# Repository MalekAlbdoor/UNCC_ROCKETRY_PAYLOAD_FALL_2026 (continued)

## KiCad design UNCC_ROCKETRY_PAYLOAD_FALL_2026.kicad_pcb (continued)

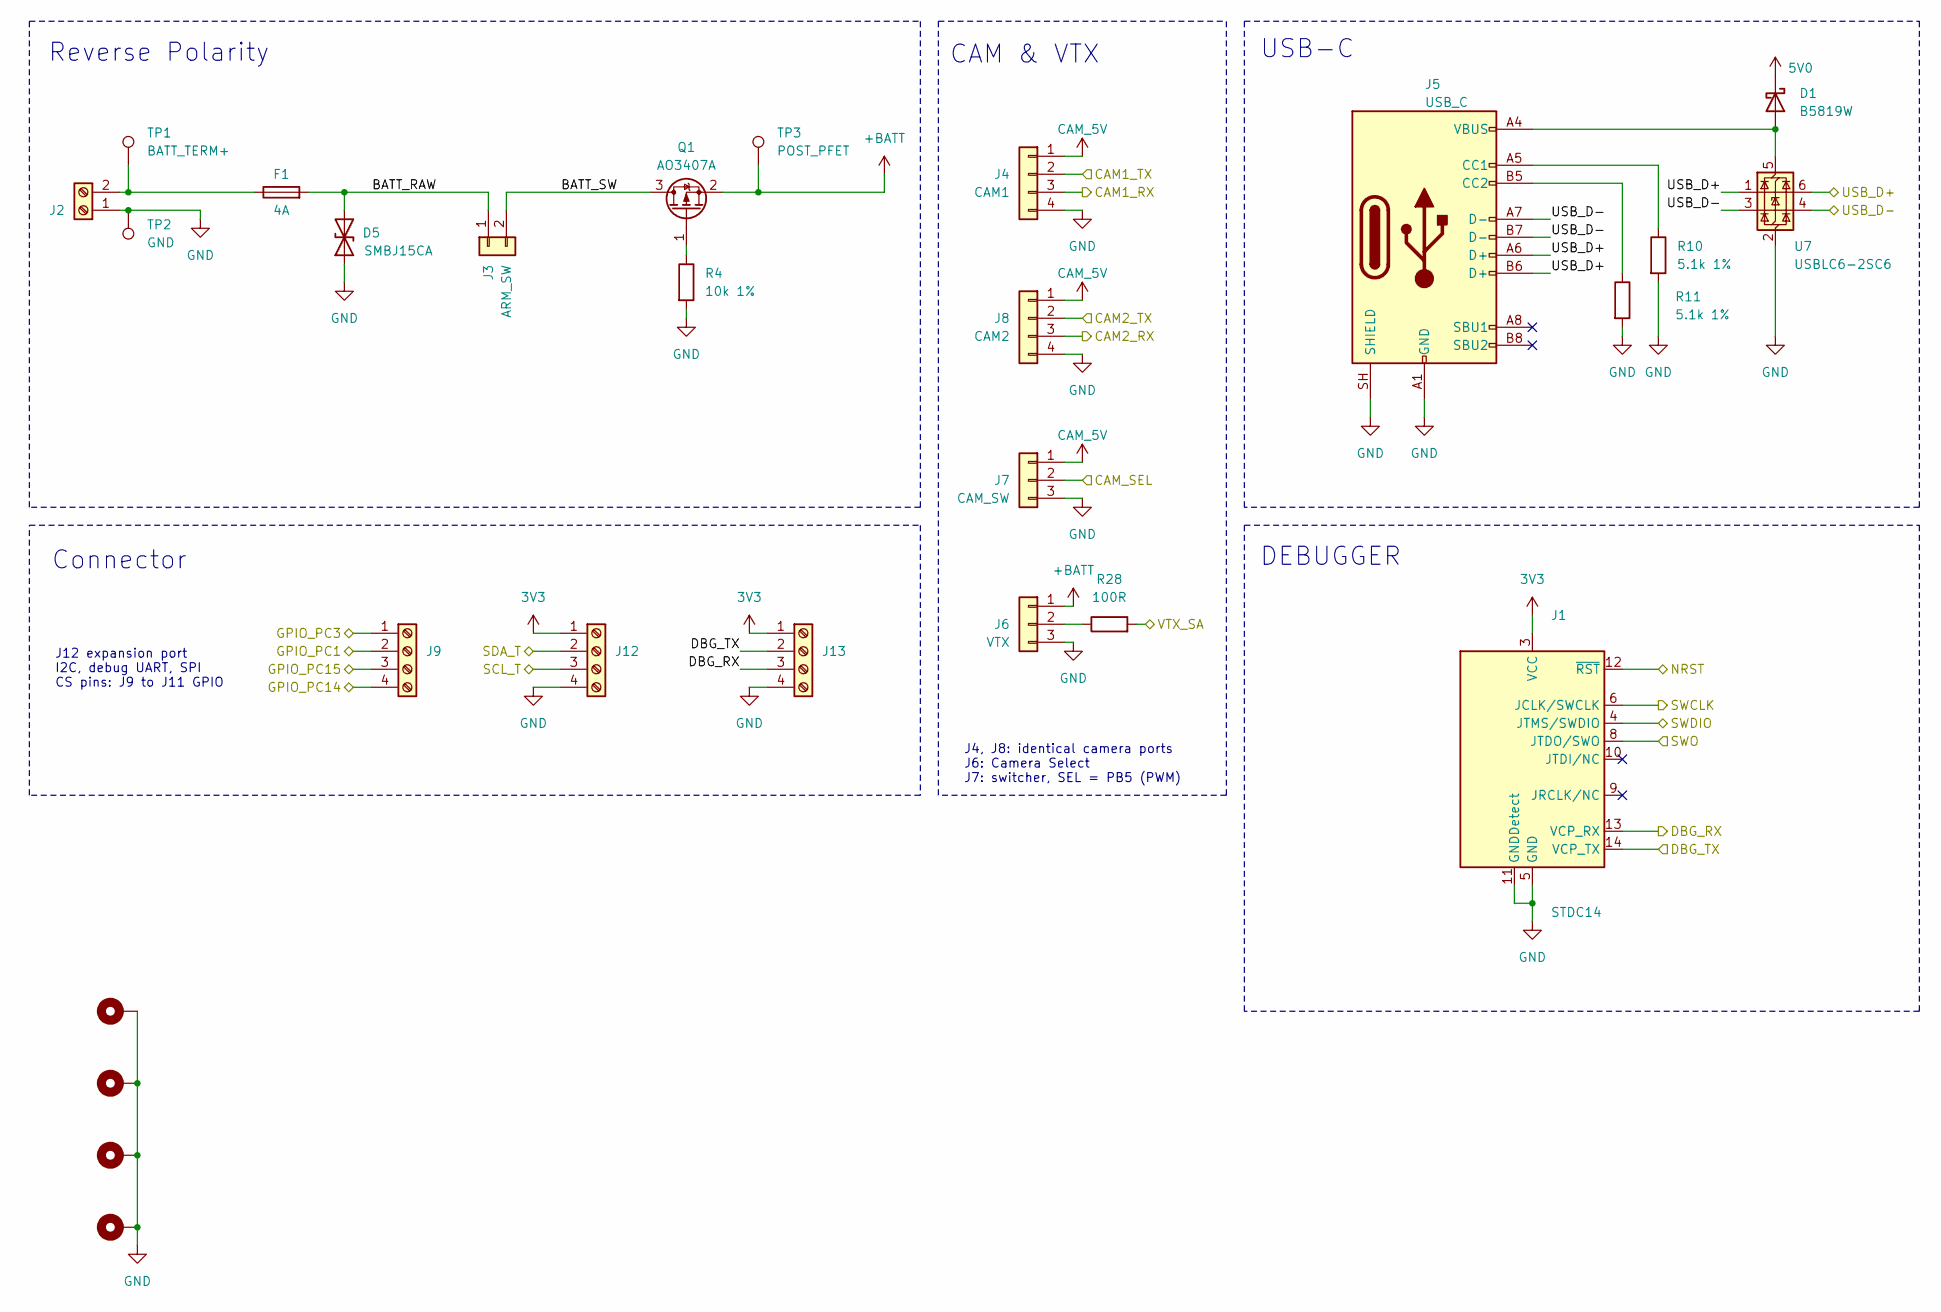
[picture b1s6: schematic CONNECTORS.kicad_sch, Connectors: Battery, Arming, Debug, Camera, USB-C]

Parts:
D1: B5819W; D_SOD-123; MPN B5819W; LCSC C7420330
D5: SMBJ15CA; D_SMB; MPN SMBJ15CA; LCSC C2760879
F1: 4A; Fuse_Littelfuse-NANO2-451_453; MPN 0451004.MRL; LCSC C27515
H2, H3, H4, H5: MountingHole_Pad; MountingHole_3.2mm_M3_Pad
J1: STDC14; PinHeader_2x07_P1.27mm_Vertical_SMD
J2: BATT; JST_XH_B2B-XH-A_1x02_P2.50mm_Vertical; MPN B2B-XH-A
J3: ARM_SW; JST_XH_B2B-XH-A_1x02_P2.50mm_Vertical; MPN B2B-XH-A
J4: CAM1; JST_PH_B4B-PH-K_1x04_P2.00mm_Vertical; MPN B4B-PH-K
J5: USB_C; USB_C_Receptacle_HRO_TYPE-C-31-M-12; MPN TYPE-C-31-M-12
J6: VTX; JST_XH_B3B-XH-A_1x03_P2.50mm_Vertical; MPN B3B-XH-A
J7: CAM_SW; JST_PH_B3B-PH-K_1x03_P2.00mm_Vertical; MPN B3B-PH-K
J8: CAM2; JST_PH_B4B-PH-K_1x04_P2.00mm_Vertical; MPN B4B-PH-K
J9, J12, J13: Screw_Terminal_01x04; TerminalBlock_Phoenix_PT-1,5-4-3.5-H_1x04_P3.50mm_Horizontal; MPN PT 1,5/4-3.5-H
Q1: AO3407A; SOT-23; MPN AO3407A; LCSC C347478
R4: 10k 1%; R_0603_1608Metric_Pad0.98x0.95mm_HandSolder; MPN 0603WAF1002T5E; LCSC C25804
R10, R11: 5.1k 1%; R_0603_1608Metric_Pad0.98x0.95mm_HandSolder; MPN 0603WAF5101T5E; LCSC C23186
R28: 100R; R_0603_1608Metric_Pad0.98x0.95mm_HandSolder; MPN 0603WAF1000T5E; LCSC C22775
TP1: BATT_TERM+; TestPoint_Pad_D1.5mm
TP2: GND; TestPoint_Pad_D1.5mm
TP3: POST_PFET; TestPoint_Pad_D1.5mm
U7: USBLC6-2SC6; SOT-23-6; MPN USBLC6-2SC6; LCSC C2827654

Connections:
3V3: J1.3 (VCC), J12.1, J13.1; also elsewhere on the board
5V0: D1.1 (K); also elsewhere on the board
+BATT: J6.1, Q1.2 (S), TP3.1 (1_1); also elsewhere on the board
/CONNECTORS/BATT_RAW: D5.2 (A2), F1.2, J3.1
/CONNECTORS/BATT_SW: J3.2, Q1.3 (D)
/CONNECTORS/CAM1_RX: J4.3; also elsewhere on the board
/CONNECTORS/CAM1_TX: J4.2; also elsewhere on the board
/CONNECTORS/CAM2_RX: J8.3; also elsewhere on the board
/CONNECTORS/CAM2_TX: J8.2; also elsewhere on the board
/CONNECTORS/CAM_SEL: J7.2; also elsewhere on the board
/CONNECTORS/DBG_RX: J1.13 (VCP_RX), J13.3; also elsewhere on the board
/CONNECTORS/DBG_TX: J1.14 (VCP_TX), J13.2; also elsewhere on the board
/CONNECTORS/GPIO_PC1: J9.2; also elsewhere on the board
/CONNECTORS/GPIO_PC3: J9.1; also elsewhere on the board
/CONNECTORS/GPIO_PC14: J9.4; also elsewhere on the board
/CONNECTORS/GPIO_PC15: J9.3; also elsewhere on the board
/CONNECTORS/NRST: J1.12 (~RST); also elsewhere on the board
/CONNECTORS/SWCLK: J1.6 (JCLK/SWCLK); also elsewhere on the board
/CONNECTORS/SWDIO: J1.4 (JTMS/SWDIO); also elsewhere on the board
/CONNECTORS/SWO: J1.8 (JTDO/SWO); also elsewhere on the board
/CONNECTORS/USB_D+: J5.A6 (D+), J5.B6 (D+), U7.1 (I/O1), U7.6 (I/O1); also elsewhere on the board
/CONNECTORS/USB_D-: J5.A7 (D-), J5.B7 (D-), U7.3 (I/O2), U7.4 (I/O2); also elsewhere on the board
/CONNECTORS/VTX_SA: R28.2; also elsewhere on the board
/SCL_T: J12.3; also elsewhere on the board
/SDA_T: J12.2; also elsewhere on the board
CAM_5V: J4.1, J7.1, J8.1; also elsewhere on the board
GND: D5.1 (A1), H2.1 (1_1), H3.1 (1_1), H4.1 (1_1), H5.1 (1_1), J1.5 (GND), J1.7 (GND), J1.11 (GNDDetect), J2.1, J4.4, J5.A1 (GND), J5.A12 (GND), J5.B1 (GND), J5.B12 (GND), J5.SH (SHIELD), J6.3, J7.3, J8.4, J12.4, J13.4, R4.2, R10.2, R11.2, TP2.1 (1_1), U7.2 (GND); also elsewhere on the board
unnamed: D1.2 (A), J5.A4 (VBUS), J5.A9 (VBUS), J5.B4 (VBUS), J5.B9 (VBUS), U7.5 (VBUS)
unnamed: F1.1, J2.2, TP1.1 (1_1)
unnamed: J5.A5 (CC1), R10.1
unnamed: J5.B5 (CC2), R11.1
unnamed: J6.2, R28.1
unnamed: Q1.1 (G), R4.1

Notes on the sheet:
USB-C
Reverse Polarity
CAM & VTX
DEBUGGER
Connector
J12 expansion port I2C, debug UART, SPI CS pins: J9 to J11 GPIO
J4, J8: identical camera ports J6: Camera Select J7: switcher, SEL = PB5 (PWM)

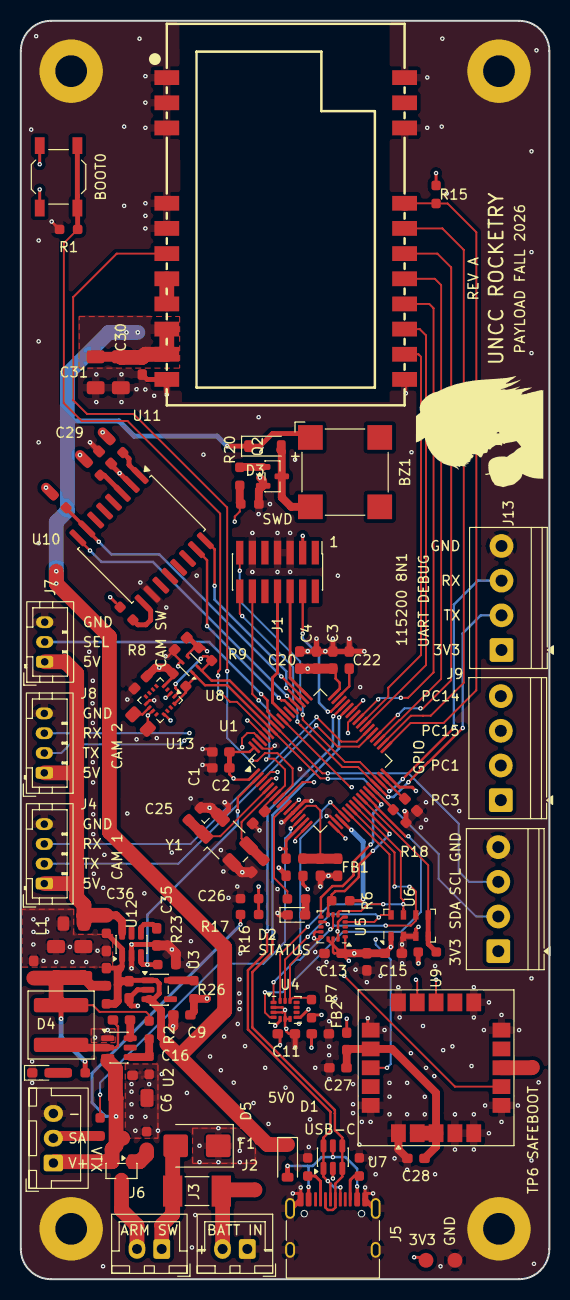
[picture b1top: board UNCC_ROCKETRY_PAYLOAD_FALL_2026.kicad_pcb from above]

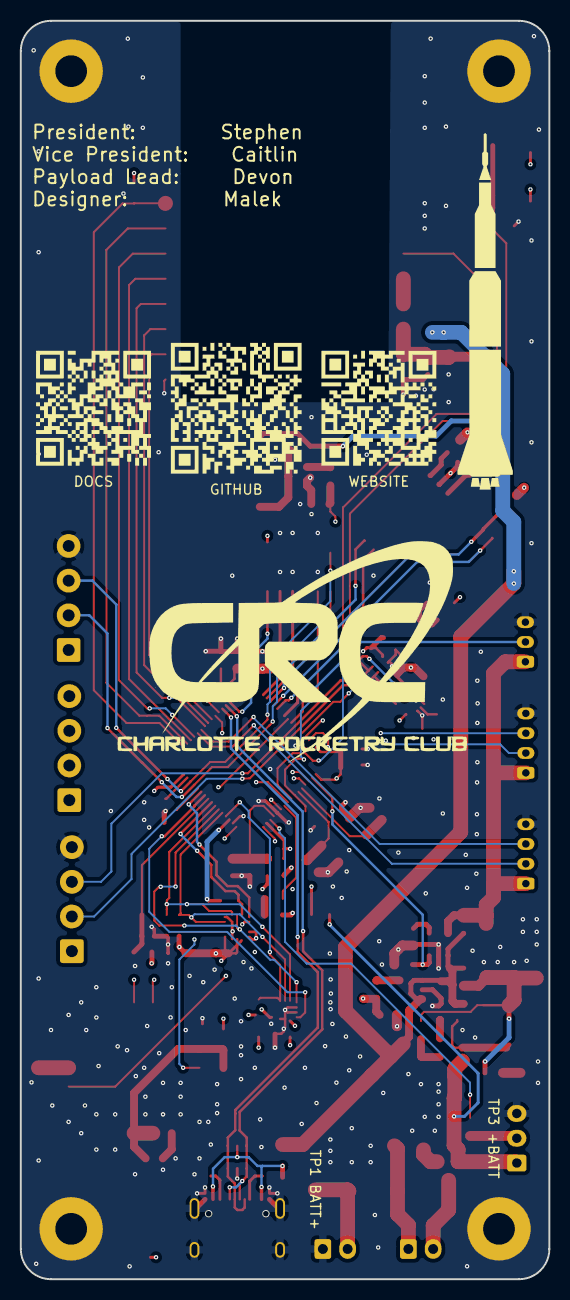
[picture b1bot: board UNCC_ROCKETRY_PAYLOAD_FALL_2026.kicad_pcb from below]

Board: 4 copper layers, 53.3 x 127.0 mm, 120 parts (5 on the bottom side), 85 nets.

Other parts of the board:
LOGO1: CRC_Logo
LOGO2: Silhouette_Logo
LOGO3: Saturn_V
LOGO4: QR_Website
LOGO5: QR_Repo
LOGO6: QR_Docs

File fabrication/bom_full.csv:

Qty,Designators,Value,Footprint,Manufacturer,MPN,LCSC,Assembly,Link
1,BZ1,CMT-8504-100-SMT,MagneticBuzzer_CUI_CMT-8504-100-SMT,CUI Devices,CMT-8504-100-SMT-TR,C22359707,JLC places,https://www.lcsc.com/search?q=C22359707
18,"C1,C2,C3,C4,C5,C7,C10,C11,C12,C13,C14,C15,C16,C24,C27,C29,C32,C33",100nF,C_0603_1608Metric_Pad1.08x0.95mm_HandSolder,YAGEO,CC0603KRX7R9BB104,C14663,JLC places,https://www.lcsc.com/search?q=C14663
1,C6,10uF 25V,C_1206_3216Metric_Pad1.33x1.80mm_HandSolder,Samsung,CL31A106KBHNNNE,C13585,JLC places,https://www.lcsc.com/search?q=C13585
5,"C8,C9,C23,C34,C38",1uF,C_0603_1608Metric_Pad1.08x0.95mm_HandSolder,Samsung,CL10A105KB8NNNC,C15849,JLC places,https://www.lcsc.com/search?q=C15849
1,C17,75pF,C_0603_1608Metric_Pad1.08x0.95mm_HandSolder,YAGEO,CC0603JRNPO9BN750,C282074,JLC places,https://www.lcsc.com/search?q=C282074
4,"C18,C19,C30,C31",22uF,C_1206_3216Metric_Pad1.33x1.80mm_HandSolder,Samsung,CL31A226KAHNNNE,C12891,JLC places,https://www.lcsc.com/search?q=C12891
2,"C20,C28",4.7uF 10V,C_0603_1608Metric_Pad1.08x0.95mm_HandSolder,Samsung,CL10A475KO8NNNC,C19666,JLC places,https://www.lcsc.com/search?q=C19666
2,"C21,C22",2.2uF 10V,C_0603_1608Metric_Pad1.08x0.95mm_HandSolder,Samsung,CL10A225KO8NNNC,C23630,JLC places,https://www.lcsc.com/search?q=C23630
2,"C25,C26",12pF C0G,C_0603_1608Metric_Pad1.08x0.95mm_HandSolder,Samsung,CL10C120JB8NNNC,C38523,JLC places,https://www.lcsc.com/search?q=C38523
1,C35,1nF,C_0603_1608Metric_Pad1.08x0.95mm_HandSolder,Samsung,CL10B102KB8NNNC,C1588,JLC places,https://www.lcsc.com/search?q=C1588
2,"C36,C37",10uF,C_0805_2012Metric_Pad1.18x1.45mm_HandSolder,Samsung,CL21A106KAYNNNE,C15850,JLC places,https://www.lcsc.com/search?q=C15850
2,"D1,D3",B5819W,D_SOD-123,,B5819W,C7420330,JLC places,https://www.lcsc.com/search?q=C7420330
1,D2,Green,LED_0603_1608Metric_Pad1.05x0.95mm_HandSolder,Everlight,19-217/G7C-AN1P2/6T,C2986030,JLC places,https://www.lcsc.com/search?q=C2986030
1,D4,Red,LED_0603_1608Metric_Pad1.05x0.95mm_HandSolder,Hubei KENTO,KT-0603R,C2286,JLC places,https://www.lcsc.com/search?q=C2286
1,D5,SMBJ15CA,D_SMB,,SMBJ15CA,C2760879,JLC places,https://www.lcsc.com/search?q=C2760879
1,F1,4A,Fuse_Littelfuse-NANO2-451_453,Littelfuse,0451004.MRL,C27515,JLC places,https://www.lcsc.com/search?q=C27515
2,"FB1,FB2",600R@100MHz,L_0603_1608Metric_Pad1.05x0.95mm_HandSolder,Sunlord,GZ1608D601TF,C1002,JLC places,https://www.lcsc.com/search?q=C1002
1,J1,STDC14,PinHeader_2x07_P1.27mm_Vertical_SMD,,,,hand solder,
1,J2,BATT,JST_XH_B2B-XH-A_1x02_P2.50mm_Vertical,JST,B2B-XH-A,,hand solder,
1,J3,ARM_SW,JST_XH_B2B-XH-A_1x02_P2.50mm_Vertical,JST,B2B-XH-A,,hand solder,
1,J4,CAM1,JST_PH_B4B-PH-K_1x04_P2.00mm_Vertical,JST,B4B-PH-K,,hand solder,
1,J5,USB_C,USB_C_Receptacle_HRO_TYPE-C-31-M-12,HRO,TYPE-C-31-M-12,,hand solder,
1,J6,VTX,JST_XH_B3B-XH-A_1x03_P2.50mm_Vertical,JST,B3B-XH-A,,hand solder,
1,J7,CAM_SW,JST_PH_B3B-PH-K_1x03_P2.00mm_Vertical,JST,B3B-PH-K,,hand solder,
1,J8,CAM2,JST_PH_B4B-PH-K_1x04_P2.00mm_Vertical,JST,B4B-PH-K,,hand solder,
3,"J9,J12,J13",Screw_Terminal_01x04,"TerminalBlock_Phoenix_PT-1,5-4-3.5-H_1x04_P3.50mm_Horizontal",Phoenix Contact,"PT 1,5/4-3.5-H",,hand solder,
1,L1,10uH,L_Wuerth_XHMI-6060,Wurth Elektronik,74439346100,C2651185,JLC places,https://www.lcsc.com/search?q=C2651185
1,Q1,AO3407A,SOT-23,Alpha & Omega,AO3407A,C347478,JLC places,https://www.lcsc.com/search?q=C347478
1,Q2,AO3400A,SOT-23,Alpha & Omega,AO3400A,C20917,JLC places,https://www.lcsc.com/search?q=C20917
11,"R1,R4,R5,R6,R7,R12,R13,R14,R15,R18,R27",10k 1%,R_0603_1608Metric_Pad0.98x0.95mm_HandSolder,UniOhm,0603WAF1002T5E,C25804,JLC places,https://www.lcsc.com/search?q=C25804
4,"R2,R16,R21,R23",100k 1%,R_0603_1608Metric_Pad0.98x0.95mm_HandSolder,UniOhm,0603WAF1003T5E,C25803,JLC places,https://www.lcsc.com/search?q=C25803
1,R3,13.3k 1%,R_0603_1608Metric_Pad0.98x0.95mm_HandSolder,UniOhm,0603WAF1332T5E,C25952,JLC places,https://www.lcsc.com/search?q=C25952
2,"R8,R9",4.7k,R_0603_1608Metric_Pad0.98x0.95mm_HandSolder,UniOhm,0603WAF4701T5E,C23162,JLC places,https://www.lcsc.com/search?q=C23162
2,"R10,R11",5.1k 1%,R_0603_1608Metric_Pad0.98x0.95mm_HandSolder,UniOhm,0603WAF5101T5E,C23186,JLC places,https://www.lcsc.com/search?q=C23186
1,R17,33k 1%,R_0603_1608Metric_Pad0.98x0.95mm_HandSolder,UniOhm,0603WAF3302T5E,C4216,JLC places,https://www.lcsc.com/search?q=C4216
1,R19,330R,R_0603_1608Metric_Pad0.98x0.95mm_HandSolder,UniOhm,0603WAF3300T5E,C23138,JLC places,https://www.lcsc.com/search?q=C23138
2,"R20,R28",100R,R_0603_1608Metric_Pad0.98x0.95mm_HandSolder,UniOhm,0603WAF1000T5E,C22775,JLC places,https://www.lcsc.com/search?q=C22775
1,R22,1k,R_0603_1608Metric_Pad0.98x0.95mm_HandSolder,UniOhm,0603WAF1001T5E,C21190,JLC places,https://www.lcsc.com/search?q=C21190
3,"R24,R25,R26",0,R_0603_1608Metric_Pad0.98x0.95mm_HandSolder,UniOhm,0603WAF0000T5E,C21189,JLC places,https://www.lcsc.com/search?q=C21189
1,SW1,BOOT0,SW_SPST_TL3342,E-Switch,TL3342F450QG,C2886897,JLC places,https://www.lcsc.com/search?q=C2886897
1,U1,STM32F405RGTx,LQFP-64_10x10mm_P0.5mm,STMicroelectronics,STM32F405RGT6,C15742,JLC places,https://www.lcsc.com/search?q=C15742
1,U2,TPS54302,SOT-23-6,Texas Instruments,TPS54302DDCR,C311983,JLC places,https://www.lcsc.com/search?q=C311983
1,U3,AP2112K-3.3,SOT-23-5,Diodes Inc,AP2112K-3.3TRG1,C23380830,JLC places,https://www.lcsc.com/search?q=C23380830
1,U4,LSM6DSO32,LGA-14_3x2.5mm_P0.5mm_LayoutBorder3x4y,STMicroelectronics,LSM6DSO32XTR,C3663738,JLC places,https://www.lcsc.com/search?q=C3663738
1,U5,H3LIS331DLTR,LGA-16_3x3mm_P0.5mm_LayoutBorder3x5y,STMicroelectronics,H3LIS331DLTR,C2655074,JLC places,https://www.lcsc.com/search?q=C2655074
1,U6,MS5611-01BA,LGA-8_3x5mm_P1.25mm,TE Connectivity,MS5611-01BA03,C37148,JLC places,https://www.lcsc.com/search?q=C37148
1,U7,USBLC6-2SC6,SOT-23-6,STMicroelectronics,USBLC6-2SC6,C2827654,JLC places,https://www.lcsc.com/search?q=C2827654
1,U8,SHT45-AD1F-R2,Sensirion_DFN-4_1.5x1.5mm_P0.8mm_SHT4x_NoCentralPad,Sensirion,SHT45-AD1F-R2,C5360602,JLC places,https://www.lcsc.com/search?q=C5360602
1,U9,SAM-M10Q-00B,ublox_SAM-M8Q,u-blox,SAM-M10Q-00B,C5443880,JLC places,https://www.lcsc.com/search?q=C5443880
1,U10,W25Q512JVFIQ,SOIC-16W_7.5x10.3mm_P1.27mm,Winbond,W25Q512JVFIQ,C2962011,JLC places,https://www.lcsc.com/search?q=C2962011
1,U11,E22-900M30S,WIRELM-SMD_E22-900M30S,EBYTE,E22-900M30S,C411294,JLC places,https://www.lcsc.com/search?q=C411294
1,U12,TPS22917DBV,SOT-23-6,Texas Instruments,TPS22917DBVR,C2681320,JLC places,https://www.lcsc.com/search?q=C2681320
1,U13,MMC5983MA,LGA-16_3x3mm_P0.5mm,MEMSIC,MMC5983MA,C404329,JLC places,https://www.lcsc.com/search?q=C404329
1,Y1,8MHz,Crystal_SMD_Abracon_ABM3B-4Pin_5.0x3.2mm,Abracon,ABM3B-8.000MHZ-10-D-1-G-T,C1985378,JLC places,https://www.lcsc.com/search?q=C1985378

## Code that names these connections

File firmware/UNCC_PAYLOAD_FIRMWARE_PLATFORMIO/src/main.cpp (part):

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  #define TX_PERIOD_MS 2000                     // a packet takes about 1.02 s on air at SF12, so 1000 never let the radio rest
#endif

const int LED = PC1;                              // silkscreen 13
SX1262 radio = new Module(PB9, PC2, PB8, PC3);    // CS 10, DIO1 12, RST 9, BUSY 11

// sensors: SPI on A0-A5, or I2C over STEMMA QT, picked at boot
SPIClass sensorSPI(PA7, PA6, PA5);                // MOSI A3, MISO A2, SCK A1
SPISettings spiCfg(1000000, MSBFIRST, SPI_MODE3);
Uart gpsSerial(PB11, PB10);                       // GPS UART on the Feather's RX, TX pins

const float G0 = 9.80665f;

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  uint8_t spiInc, i2cInc;                         // auto-increment bit for multi-byte reads
  Bus bus; uint8_t addr;
};
Sensor imu  = {"LSM6DSO32", PA4, {0x6A, 0x6B}, 0x6C, 0x00, 0x00, NONE, 0};   // CS A0
Sensor hig  = {"H3LIS331",  PC4, {0x18, 0x19}, 0x32, 0x40, 0x80, NONE, 0};   // CS A4
Sensor baro = {"MS5611",    PC5, {0x77, 0x76}, 0,    0,    0,    NONE, 0};   // CS A5, no WHO_AM_I
uint8_t shtAddr = 0;                              // SHT45 at 0x44 when found
uint8_t gpsI2C = 0;                               // 0x42 when the GPS answers on I2C, else UART only

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}

// ---------- battery ----------
// The Feather has a 100k/100k divider from BAT to A6 (PA3). On the payload PCB it is VBAT_SENSE
// on PA1 through 100k/33k, sized for a 2S pack, so switch these two lines for the PCB.
const uint32_t VBAT_PIN = PA3;
const float VBAT_DIV = 2.0f;                      // PCB: (100k + 33k) / 33k
float vbat = 0;                                   // volts, about a 1 s average

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
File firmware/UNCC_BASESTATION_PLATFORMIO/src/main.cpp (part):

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#include <Adafruit_SSD1306.h>

// Wio-SX1262 on the XIAO ESP32-S3
#define LORA_SCK   7
#define LORA_MISO  8
#define LORA_MOSI  9
#define LORA_CS    41
#define LORA_RST   42
#define LORA_DIO1  39
#define LORA_BUSY  40
#define LORA_RXEN  38

// OLED on the XIAO's I2C pins
#define OLED_SDA   5     // silkscreen D4
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    while (true) { Serial.printf("radio failed, code %d\n", s); delay(2000); }
  }
  radio.setDio2AsRfSwitch(true);
  radio.setRfSwitchPins(LORA_RXEN, RADIOLIB_NC);
  radio.setCurrentLimit(140);
  radio.setRxBoostedGainMode(true);
  radio.setPacketReceivedAction(onRx);
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
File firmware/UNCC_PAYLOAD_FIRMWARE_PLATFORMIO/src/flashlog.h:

#pragma once
#include <Arduino.h>
#include <SPI.h>

// Flight log on the W25Q512JV (64 MB NOR) on SPI3, as wired on the payload PCB:
//   CLK PC10, DO (MISO) PC11, DI (MOSI) PC12, CS PA15.
//
// Layout: 3 telemetry records per 256 byte page (3 x 77 = 231 bytes, the other 25 stay 0xFF),
// written one page at a time from the start of the chip. Every page therefore starts with a
// record whose first byte is the magic 'X', and an erased page starts with 0xFF, so at boot the
// end of the log is found with a binary search and logging carries on after it. Nothing is ever
// erased while the rocket is running; the flash is only erased by the 'E' command on the ground.
//
// Page programs are started and not waited for (0.4 to 3 ms); the next flash command waits for
// the chip to be idle first, so the 400 Hz sensor loop is not held up.

#define FL_REC       77
#define FL_PAGE      256
#define FL_PER_PAGE  3
#define FL_CAP       (64UL * 1024 * 1024)
#define FL_PAGES     (FL_CAP / FL_PAGE)
#define FL_BLOCK     65536UL

SPIClass flashSPI(PC12, PC11, PC10);                // MOSI, MISO, SCK
const int FLASH_CS = PA15;
SPISettings flashCfg(10000000, MSBFIRST, SPI_MODE0);

bool flReady = false;
uint32_t flPage = 0;                                // next page to program
uint8_t flBuf[FL_PAGE];
uint8_t flN = 0;                                    // records waiting in flBuf

static inline void flSel()   { flashSPI.beginTransaction(flashCfg); digitalWrite(FLASH_CS, LOW); }
static inline void flDesel() { digitalWrite(FLASH_CS, HIGH); flashSPI.endTransaction(); }

static void flCmd(uint8_t op) { flSel(); flashSPI.transfer(op); flDesel(); }

static void flAddr(uint8_t op, uint32_t a) {        // opcode and 4 address bytes, CS left low
  flSel();
  flashSPI.transfer(op);
  flashSPI.transfer(a >> 24); flashSPI.transfer(a >> 16); flashSPI.transfer(a >> 8); flashSPI.transfer(a);
}

static uint8_t flStatus() { flSel(); flashSPI.transfer(0x05); uint8_t s = flashSPI.transfer(0); flDesel(); return s; }

static bool flWait(uint32_t timeoutMs = 3000) {
  uint32_t t = millis();
  while (flStatus() & 1) if (millis() - t > timeoutMs) return false;
  return true;
}

static void flRead(uint32_t a, uint8_t *buf, uint16_t n) {
  flWait();
  flAddr(0x13, a);                                  // read, 4 byte address
  for (uint16_t i = 0; i < n; i++) buf[i] = flashSPI.transfer(0);
  flDesel();
}

static void flProgram(uint32_t a, const uint8_t *d, uint16_t n) {   // within one page; not waited for
  flWait();
  flCmd(0x06);                                      // write enable
  flAddr(0x12, a);                                  // page program, 4 byte address
  for (uint16_t i = 0; i < n; i++) flashSPI.transfer(d[i]);
  flDesel();
}

static bool flEraseBlock(uint32_t a) {              // 64 KB, 150 ms typical
  flWait();
  flCmd(0x06);
  flAddr(0xDC, a);
  flDesel();
  return flWait(3000);
}

// first erased page after the log; false if the chip is not there
bool flBegin() {
  pinMode(FLASH_CS, OUTPUT); digitalWrite(FLASH_CS, HIGH);
  flashSPI.begin();
  flCmd(0x66); flCmd(0x99); delay(1);               // reset
  flSel(); flashSPI.transfer(0x9F);
  uint8_t mfr = flashSPI.transfer(0), type = flashSPI.transfer(0), cap = flashSPI.transfer(0);
  flDesel();
  if (mfr != 0xEF || type != 0x40 || cap != 0x20) return false;   // Winbond W25Q512JV
  flCmd(0xB7);                                      // 4 byte addressing

  uint32_t lo = 0, hi = FL_PAGES;                   // pages before the end start with 'X', after it with 0xFF
  while (lo < hi) {
    uint32_t mid = (lo + hi) / 2;
    uint8_t b;
    flRead(mid * FL_PAGE, &b, 1);
    if (b == 0xFF) hi = mid; else lo = mid + 1;
  }
  flPage = lo;
  // a power cut in the middle of a page program leaves a page that starts blank but isn't; skip those
  for (; flPage < FL_PAGES; flPage++) {
    uint8_t p[FL_PAGE];
    flRead(flPage * FL_PAGE, p, FL_PAGE);
    bool blank = true;
    for (uint16_t i = 0; i < FL_PAGE && blank; i++) blank = p[i] == 0xFF;
    if (blank) break;
  }
  flN = 0;
  return flReady = true;
}

static void flFlush() {                             // write whatever is waiting, even a part page
  if (!flN || flPage >= FL_PAGES) return;
  flProgram(flPage * FL_PAGE, flBuf, flN * FL_REC);
  flPage++;
  flN = 0;
}

bool flAppend(const void *rec) {
  if (!flReady || flPage >= FL_PAGES) return false;
  memcpy(flBuf + flN * FL_REC, rec, FL_REC);
  if (++flN == FL_PER_PAGE) flFlush();
  return true;
}

uint32_t flUsedBytes() { return (flPage + (flN ? 1 : 0)) * FL_PAGE; }

static uint32_t crcUpdate(uint32_t c, const uint8_t *d, uint16_t n) {   // standard CRC-32, same as zlib.crc32
  static const uint32_t t[16] = {0x00000000, 0x1DB71064, 0x3B6E20C8, 0x26D930AC, 0x76DC4190, 0x6B6B51F4, 0x4DB26158, 0x5005713C, 0xEDB88320, 0xF00F9344, 0xD6D6A3E8, 0xCB61B38C, 0x9B64C2B0, 0x86D3D2D4, 0xA00AE278, 0xBDBDF21C};
  for (uint16_t i = 0; i < n; i++) {
    c ^= d[i];
    c = (c >> 4) ^ t[c & 15];
    c = (c >> 4) ^ t[c & 15];
  }
  return c;
}

// "DUMP <bytes>\n", the raw pages, then "\nCRC <hex>\n"
void flDump(Stream &out) {
  flFlush();
  uint32_t n = flPage * FL_PAGE, crc = 0xFFFFFFFF;
  out.print("DUMP "); out.print(n); out.print("\n");
  uint8_t p[FL_PAGE];
  for (uint32_t a = 0; a < n; a += FL_PAGE) {
    flRead(a, p, FL_PAGE);
    crc = crcUpdate(crc, p, FL_PAGE);
    out.write(p, FL_PAGE);
  }
  out.print("\nCRC "); out.printf("%08lx", (unsigned long)~crc); out.print("\n");
}

// erase everything that has been written, 64 KB at a time (the chip erase command takes minutes)
bool flEraseAll(Stream &out) {
  flFlush();
  uint32_t blocks = (flUsedBytes() + FL_BLOCK - 1) / FL_BLOCK;
  for (uint32_t b = 0; b < blocks; b++) {
    if (!flEraseBlock(b * FL_BLOCK)) { out.println("\nerase timed out"); return false; }
    if (b % 16 == 15) out.print('.');
  }
  flPage = 0; flN = 0;
  return true;
}
